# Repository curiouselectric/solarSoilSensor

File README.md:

# solarSoilSensor
An ATTiny85 based soil moisture sensor for plants

This repository contains:
* Instructions
* Schematic
* PCB files (KiCAD) & Gerbers
* HEX file

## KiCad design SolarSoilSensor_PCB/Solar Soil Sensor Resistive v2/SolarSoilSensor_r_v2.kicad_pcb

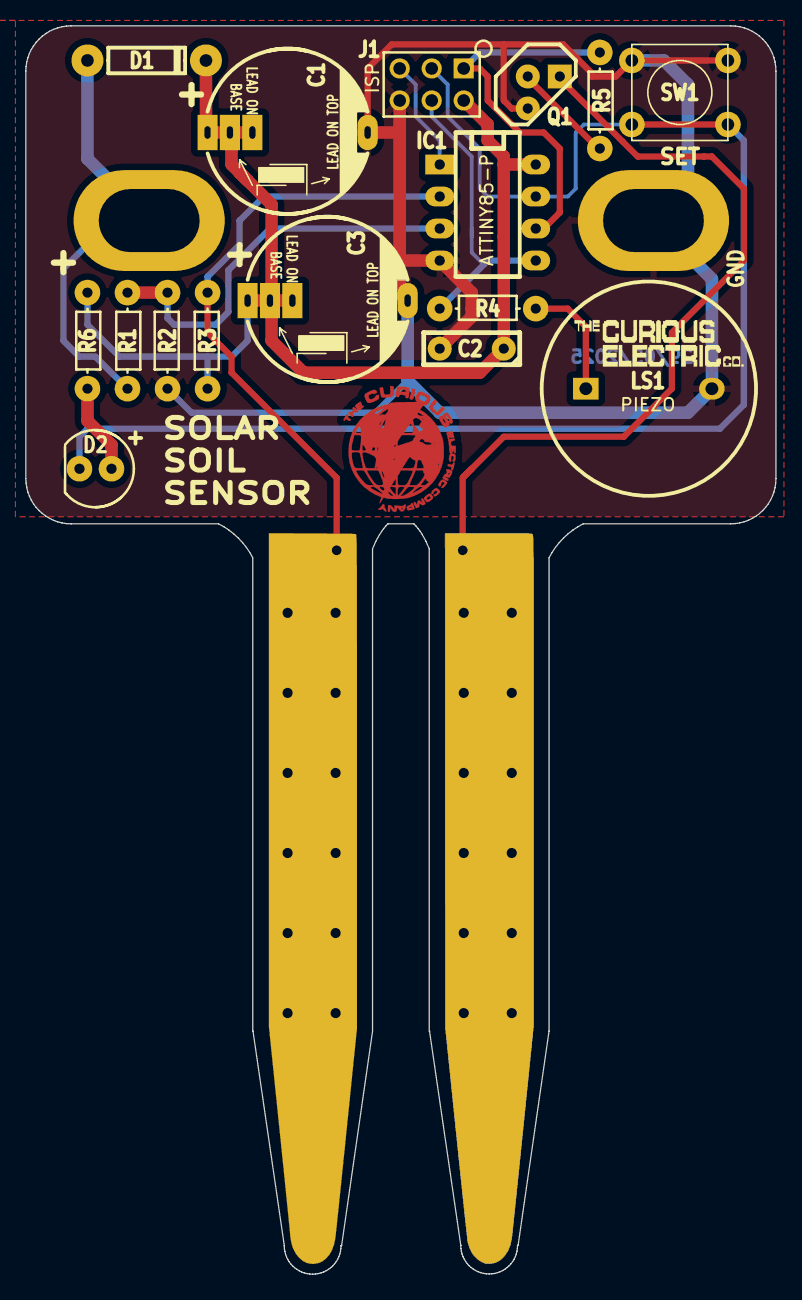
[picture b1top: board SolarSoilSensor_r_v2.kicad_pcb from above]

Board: 2 copper layers, 59.5 x 99.0 mm, 20 parts (1 on the bottom side), 13 nets.

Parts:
C1, C3: 0.47F; C_0_47F_SuperCap_3POS
C2: 100n; C1_wide_lg_pad
D1: 1N5819; TH_Diode_1
D2: LED; LED-5MM_larg_pad_REV
IC1: ATTINY85-P; DIP-8_300_ELL
J1: ISP; TH3x2_ISP
LS1: PIEZO; TH_PIEZO_17x7
P3: SOIL_SENSOR; 2020_04_14_SolarSoilSensorPCB_Outline_linkedpad
P7: LOGO1; 2020_04_14_CuriousElectricCompany_Logo_Round_10mm_FCu
P8: LOGO2; TCEC_Words_13mm
Q1: BC547; TO92-EBC_large_pad
R1: 470k; TH_Resistor_1
R2: 10k; TH_Resistor_1
R3: 100k; TH_Resistor_1
R4: 120; TH_Resistor_1
R5: 1k; TH_Resistor_1
R6: 330; TH_Resistor_1
SC1: SOLAR PV; PV_53x30mm_Area
SW1: SET; SW_PUSH_SMALL_lg_pad

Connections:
/LED: D2.1 (K), IC1.7 (PB2(SCK/USCK/SCL/T0/INT0/ADC1/PCINT2)), J1.3, SW1.2
/PIEZO: IC1.5 (PB0(MOSI/DI/SDA/AIN0/OC0A/OC1A/AREF/PCI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), J1.4, R4.1
/SOIL_POWER: IC1.6 (PB1(MISO/DO/AIN1/OC0B/OC1A/PCINT1)), J1.1, R5.1
/SOIL_SENSE: IC1.2 (PB3(XTAL1/CLKI/OC1B/ADC3/PCINT3)), P3.1, R3.2
/Vsolar: IC1.3 (PB4(XTAL2/CLKO/OC1B/ADC2/PCINT4)), R1.1, R2.2
GND: C1.2, C2.2, C3.2, IC1.4 (GND), J1.6, LS1.2, Q1.3 (E), R2.1, SC1.2 (-), SW1.1
unnamed: D1.2 (A), R1.2, SC1.1 (+)
unnamed: D2.2 (A), R6.2
unnamed: IC1.1 (PB5(~RESET/dW/ADC0/PCINT5)), J1.5
unnamed: LS1.1, R4.2
unnamed: P3.2, Q1.1 (C)
unnamed: Q1.2 (B), R5.2
VCC: C1.1, C2.1, C3.1, D1.1 (K), IC1.8 (VCC), J1.2, R3.1, R6.1

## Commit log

2020-07-09 main file upload
2025-06-11 Updated with version 2. Changes to all files
2025-06-11 name change
2025-06-27 updated instructions with new pv install technique
2025-06-27 updated pdf instructions
2025-06-27 updated instructions
